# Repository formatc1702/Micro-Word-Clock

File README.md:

Micro-Word-Clock
================

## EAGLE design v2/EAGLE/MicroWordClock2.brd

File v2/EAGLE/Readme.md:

Micro Word Clock v2 EAGLE files
===============================

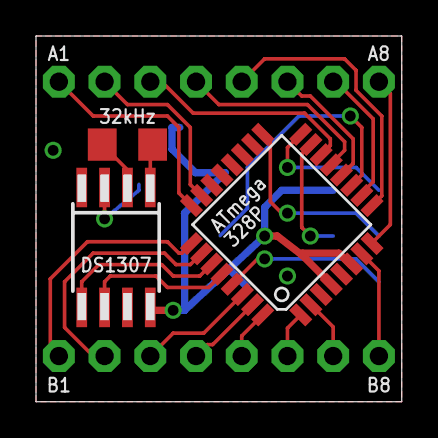
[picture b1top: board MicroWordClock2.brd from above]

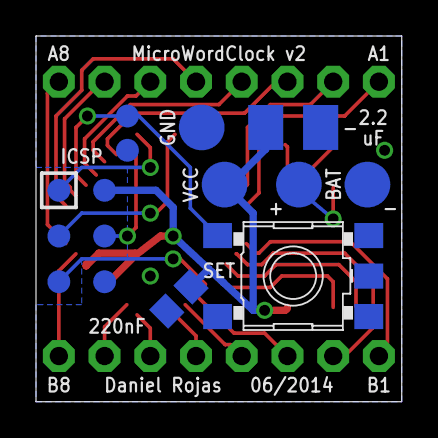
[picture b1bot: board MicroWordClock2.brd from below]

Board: 2 copper layers, 20.3 x 20.3 mm, 20 parts (15 on the bottom side), 28 nets.

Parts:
C1: 220nF; C0805
C2: 2.2uF; B/3528-21R
IC1: ATMEGA328P; TQFP32-08
IC2: DS1307SMD; SO-08M
JP_A: 1X08-CLEANBIG
JP_B: 1X08-CLEANBIG
S1: SKHMPSE010; SKHMPXE010
TP_BAT+: TPB2,54; B2,54
TP_BAT-: TPB2,54; B2,54
TP_GND: TPB1,27; B1,27
TP_GND1: TPB2,54; B2,54
TP_MISO: TPB1,27; B1,27
TP_MOSI: TPB1,27; B1,27
TP_RST: TPB1,27; B1,27
TP_SCK: TPB1,27; B1,27
TP_SWITCH: TPB1,27; B1,27
TP_SWITCH_GND: TPB1,27; B1,27
TP_VCC: TPB1,27; B1,27
TP_VCC1: TPB2,54; B2,54
XTAL: XTAL-32KHZ; XTAL-SMD-1206-3216M

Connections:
+5V: C1.1, C2.+, IC1.4, IC1.6, IC2.8, TP_VCC.TP, TP_VCC1.TP
A1: IC1.24, JP_A.1
A2: IC1.23, JP_A.2
A3: IC1.14, JP_A.3
A4: IC1.13, JP_A.4
A5: IC1.9, JP_A.5
A6: IC1.12, JP_A.6
A7: IC1.10, JP_A.7
A8: IC1.8, JP_A.8
B1: IC1.25, JP_B.1
B2: IC1.26, JP_B.2
B3: IC1.30, JP_B.3
B4: IC1.31, JP_B.4
B5: IC1.32, JP_B.5
B6: IC1.1, JP_B.6
B7: IC1.2, JP_B.7
B8: IC1.7, JP_B.8
GND: C1.2, C2.-, IC1.3, IC1.5, IC1.21, IC2.4, S1.3, S1.4, S1.5, TP_BAT-.TP, TP_GND.TP, TP_GND1.TP, TP_SWITCH_GND.TP
MISO: IC1.16, TP_MISO.TP
MOSI: IC1.15, TP_MOSI.TP
unnamed: IC2.2, XTAL.X1
unnamed: IC2.1, XTAL.X2
unnamed: IC1.28, IC2.6
RESET: IC1.29, TP_RST.TP
SCK: IC1.17, TP_SCK.TP
SDA: IC1.27, IC2.5
SWITCH: IC1.11, S1.1, TP_SWITCH.TP
VBAT: IC2.3, TP_BAT+.TP

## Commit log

2014-12-03 Create aaa
2014-12-03 Rename Graphics/Readme.md to v2/Graphics/Readme.md
2014-12-03 Initial upload of files
2014-12-03 Removed unnecessary Readme.md's
2014-12-03 Removed more unnecessary Readme.md's
2014-12-03 Merge branch 'master' of https://github.com/formatc1702/Micro-Word-Clock
    Conflicts:
    v2/Readme.md
2014-12-04 Add dutch
2014-12-08 Added RTClib library
2014-12-08 Added boards.txt
2014-12-08 Added graphics for Dutch version by qistoph
2014-12-30 Added another dutch layout
2015-12-07 Added Gerber Files
2016-01-07 Added CC BY-SA license
2016-10-13 Reorder files and update Readme.
2016-10-13 Improve BOM
2016-10-15 Add .gitignore
2019-07-14 Fixed Link
    Fixed link to reichelt
